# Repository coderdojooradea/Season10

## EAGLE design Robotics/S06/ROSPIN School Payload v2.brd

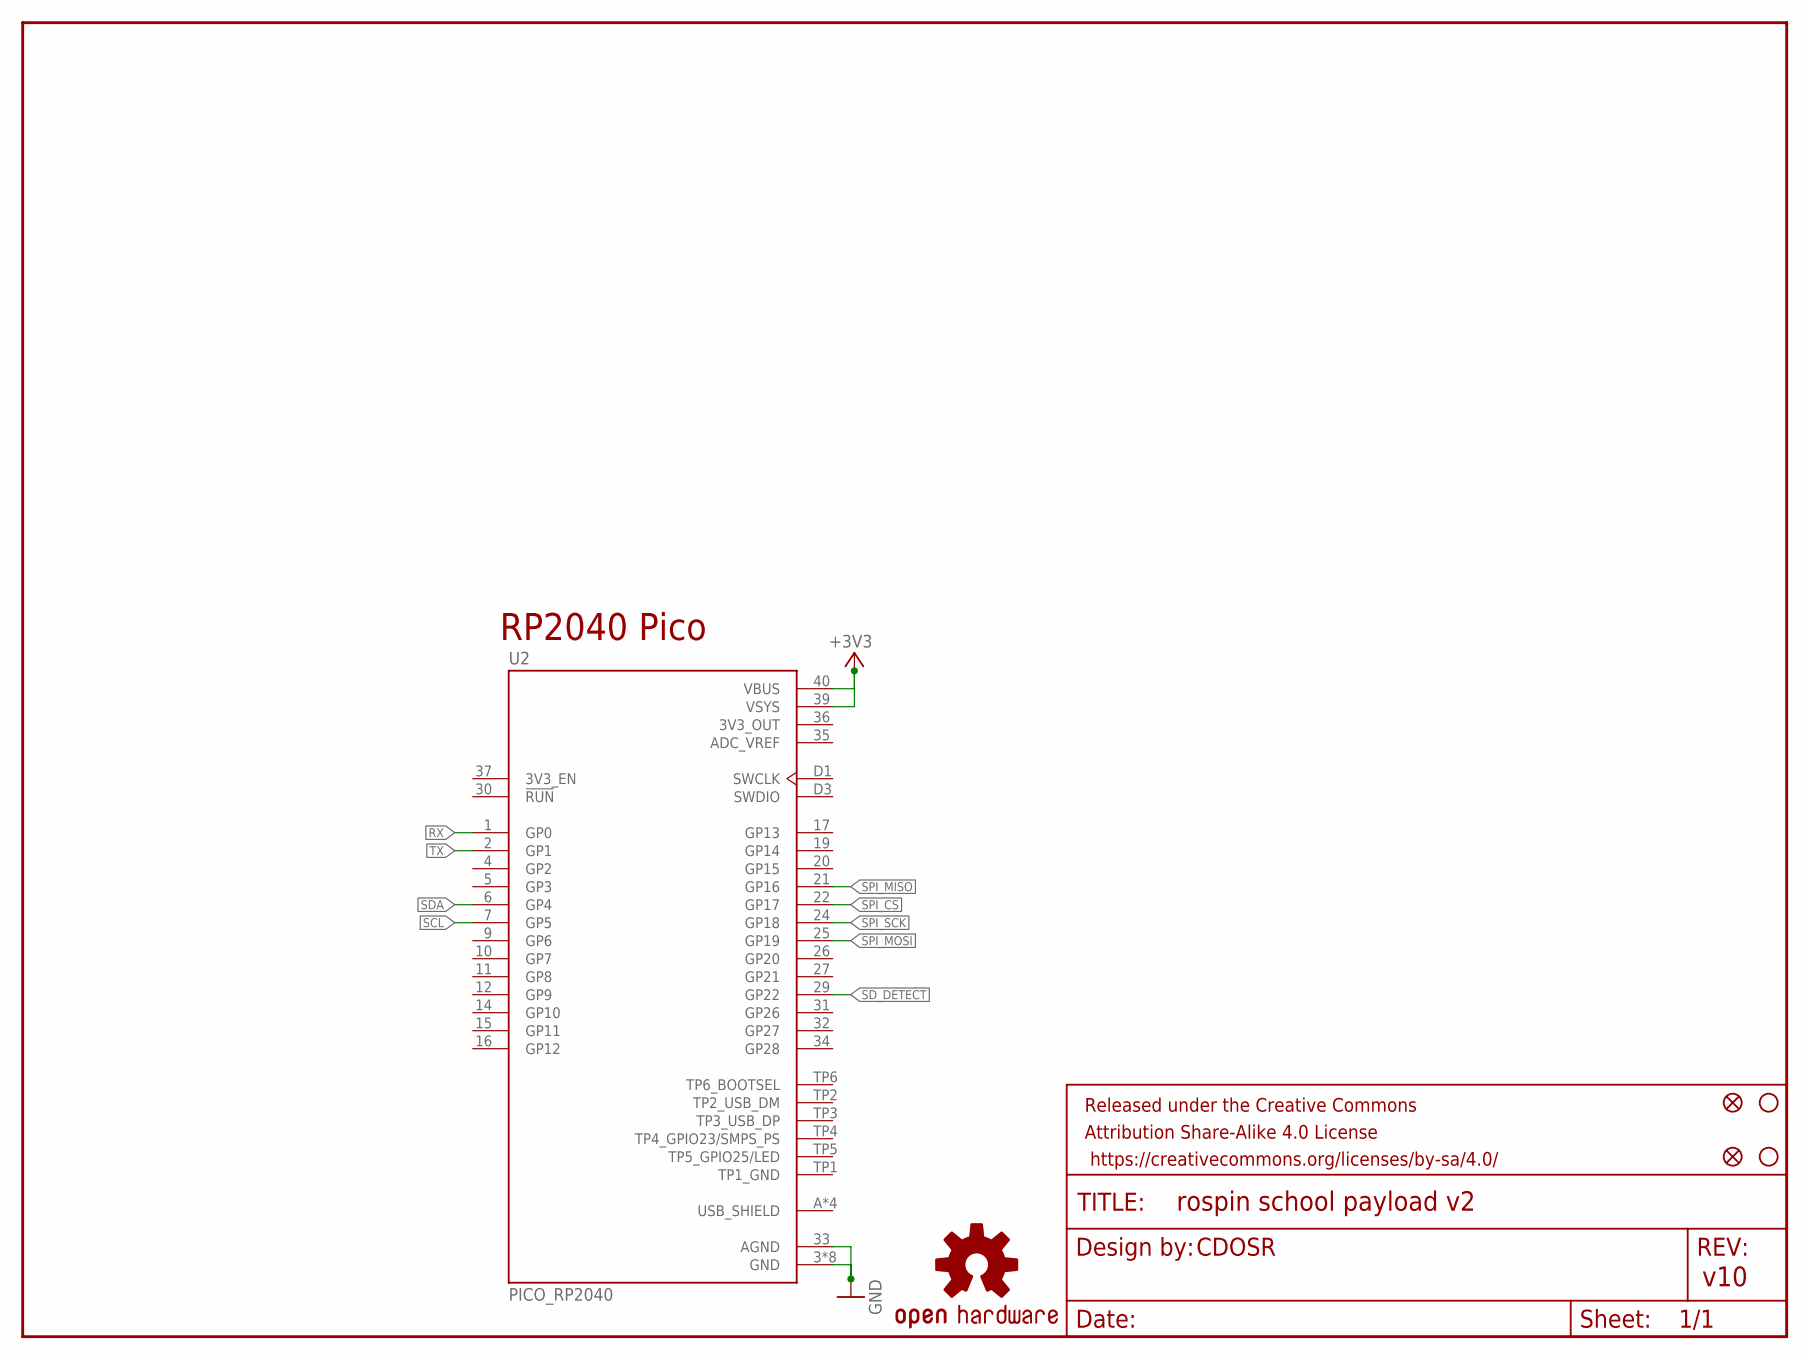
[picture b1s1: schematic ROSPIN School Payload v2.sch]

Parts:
FID1, FID2: FIDUCIAL1X2; FIDUCIAL-1X2
FRAME1: FRAME-LETTER; CREATIVE_COMMONS
LOGO2: OSHW-LOGOS; OSHW-LOGO-S
STANDOFF1, STANDOFF2: STAND-OFF
U2: PICO_RP2040; MODULE_PICO_RP2040

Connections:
3V3_OUT: U2.36 (3V3_OUT)
+3V3: U2.39 (VSYS), U2.40 (VBUS)
ADC_VREF: U2.35 (ADC_VREF)
GND: U2.3 (GND), U2.8 (GND), U2.13 (GND), U2.18 (GND), U2.23 (GND), U2.28 (GND), U2.33 (AGND), U2.38 (GND), U2.D2 (GND)
RX: U2.1 (GP0)
SCL: U2.7 (GP5)
SDA: U2.6 (GP4)
SD_DETECT: U2.29 (GP22)
SPI_CS: U2.22 (GP17)
SPI_MISO: U2.21 (GP16)
SPI_MOSI: U2.25 (GP19)
SPI_SCK: U2.24 (GP18)
TP1_GND: U2.TP1 (TP1_GND)
TX: U2.2 (GP1)
USB_SHIELD: U2.A (USB_SHIELD), U2.B (USB_SHIELD), U2.C (USB_SHIELD), U2.D (USB_SHIELD)

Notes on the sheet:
RP2040 Pico

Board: 2 copper layers, 7 parts (1 on the bottom side), 3 nets, no tracks yet.

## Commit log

2023-09-24 Initial project
2023-10-08 Update TODOs
2023-10-08 Update options key in scenario
2023-10-22 Update scenarios_template

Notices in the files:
parts and their libraries:
SparkFun-Aesthetics: Licensing: Creative Commons ShareAlike 4.0 International - https://creativecommons.org/licenses/by-sa/4.0
SparkFun-Aesthetics: Released under the Creative Commons Attribution Share-Alike 4.0 License
SparkFun-Aesthetics: https://creativecommons.org/licenses/by-sa/4.0
